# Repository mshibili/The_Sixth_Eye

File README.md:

# The_Sixth_Eye
ATmega328 low power based Ultrasonic sensor eye for visually impaired.

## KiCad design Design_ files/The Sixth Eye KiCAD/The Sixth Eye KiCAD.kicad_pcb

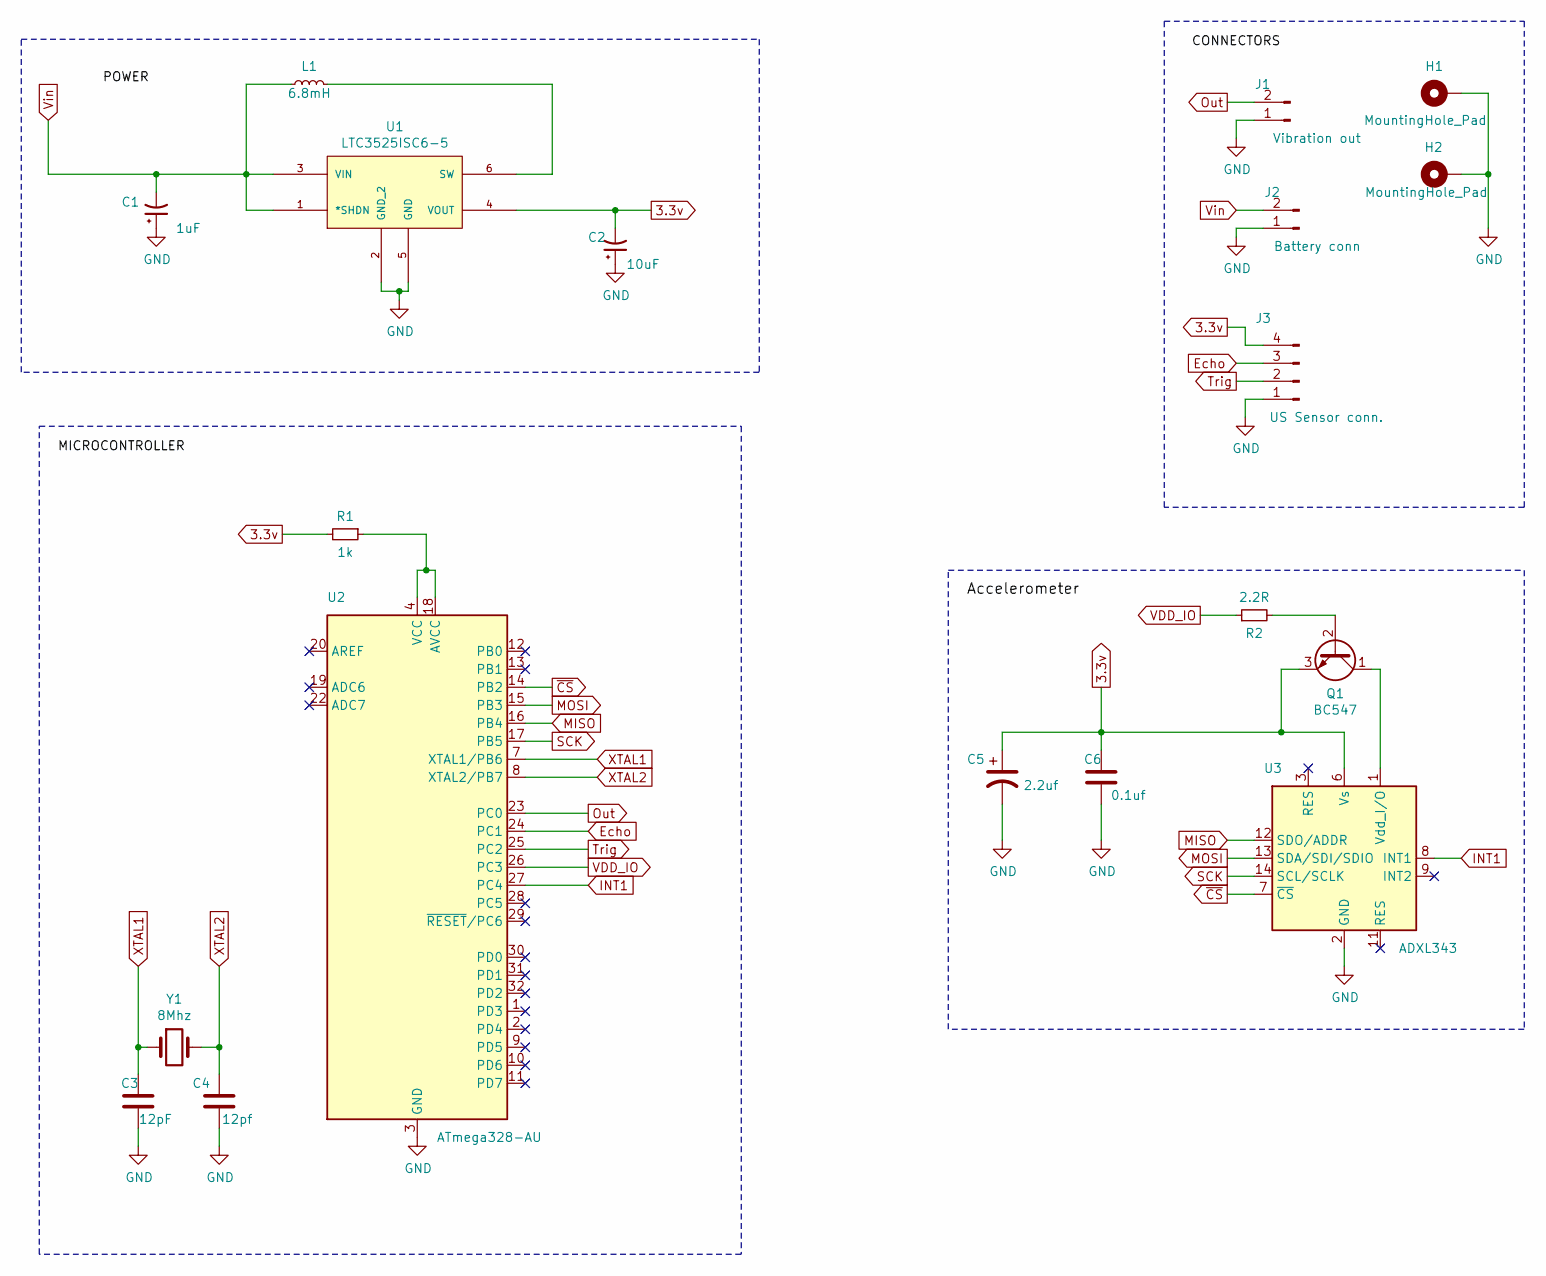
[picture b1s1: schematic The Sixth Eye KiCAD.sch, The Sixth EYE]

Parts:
C1: 1uF; CP_EIA-3216-18_Kemet-A_Pad1.58x1.35mm_HandSolder
C2: 10uF; CP_EIA-6032-20_AVX-F_Pad2.25x2.35mm_HandSolder
C3: 12pF; C_0805_2012Metric_Pad1.18x1.45mm_HandSolder
C4: 12pf; C_0805_2012Metric_Pad1.18x1.45mm_HandSolder
C5: 2.2uf; CP_EIA-1608-10_AVX-L
C6: 0.1uf; CP_EIA-1608-08_AVX-J
H1, H2: MountingHole_Pad; MountingHole_2.2mm_M2_DIN965_Pad_TopBottom
J1: Vibration out; PinSocket_1x02_P2.00mm_Horizontal
J2: Battery conn; PhoenixContact_MC_1,5_2-G-3.5_1x02_P3.50mm_Horizontal
J3: US Sensor conn.; PinHeader_1x04_P1.27mm_Vertical_SMD_Pin1Left
L1: 6.8mH; L_1210_3225Metric
Q1: BC547; SOT-23
R1: 1k; R_1206_3216Metric
R2: 2.2R; R_0603_1608Metric_Pad0.98x0.95mm_HandSolder
U1: LTC3525ISC6-5; SC-70-8_Handsoldering
U2: ATmega328-AU; TQFP-32_7x7mm_P0.8mm
U3: ADXL343; LGA-14_3x5mm_P0.8mm_LayoutBorder1x6y
Y1: 8Mhz; Crystal_SMD_HC49-SD

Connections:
3.3v: C2.2, C5.1, C6.1, J3.4, Q1.3 (E), R1.2, U1.4 (VOUT), U3.6 (Vs)
Echo: J3.3, U2.24 (PC1)
GND: C1.1, C2.1, C3.2, C4.2, C5.2, C6.2, H1.1, H2.1, J1.1, J2.1, J3.1, U1.2 (GND_2), U1.5 (GND), U2.3 (GND), U2.5 (GND), U2.21 (GND), U3.2 (GND), U3.4 (GND), U3.5 (GND)
INT1: U2.27 (PC4), U3.8 (INT1)
MISO: U2.16 (PB4), U3.12 (SDO/ADDR)
MOSI: U2.15 (PB3), U3.13 (SDA/SDI/SDIO)
unnamed: L1.2, U1.6 (SW)
unnamed: Q1.1 (C), U3.1 (Vdd_I/O)
unnamed: Q1.2 (B), R2.2
unnamed: R1.1, U2.4 (VCC), U2.6 (VCC), U2.18 (AVCC)
Out: J1.2, U2.23 (PC0)
SCK: U2.17 (PB5), U3.14 (SCL/SCLK)
Trig: J3.2, U2.25 (PC2)
VDD_IO: R2.1, U2.26 (PC3)
Vin: C1.2, J2.2, L1.1, U1.1 (*SHDN), U1.3 (VIN)
XTAL1: C3.1, U2.7 (XTAL1/PB6), Y1.1
XTAL2: C4.1, U2.8 (XTAL2/PB7), Y1.2
~CS: U2.14 (PB2), U3.7 (~CS)

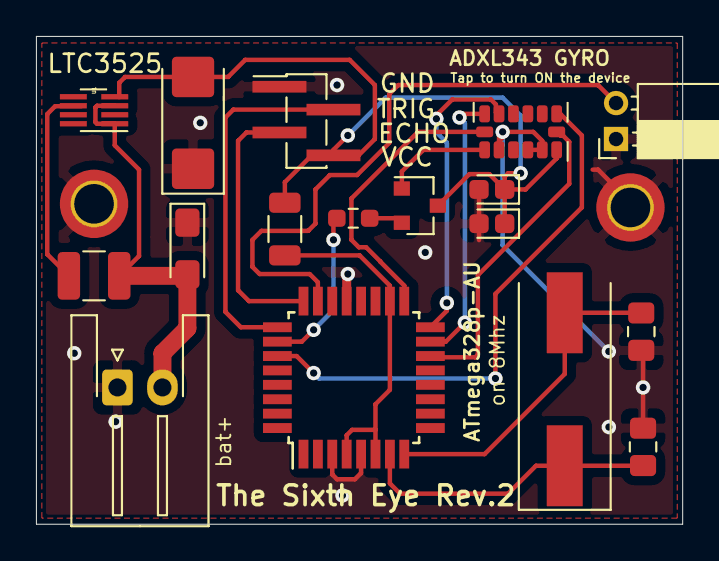
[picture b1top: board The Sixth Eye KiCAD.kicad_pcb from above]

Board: 2 copper layers, 35.9 x 27.1 mm, 19 parts (0 on the bottom side), 18 nets.

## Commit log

2021-07-31 PCB completed
2021-07-31 ploted
2021-07-31 gerbers & drill files
2021-08-01 sixth_eye.ino updated
2021-08-02 firmware update
2021-08-03 Accelerometer added to schematics
2021-08-03 Accelrometer pcb
2021-08-03 v2 completed
2021-08-04 KiCAD Pcb completed for Sixth_Eye including Accelerometer
2023-01-17 Repo Migration Update
